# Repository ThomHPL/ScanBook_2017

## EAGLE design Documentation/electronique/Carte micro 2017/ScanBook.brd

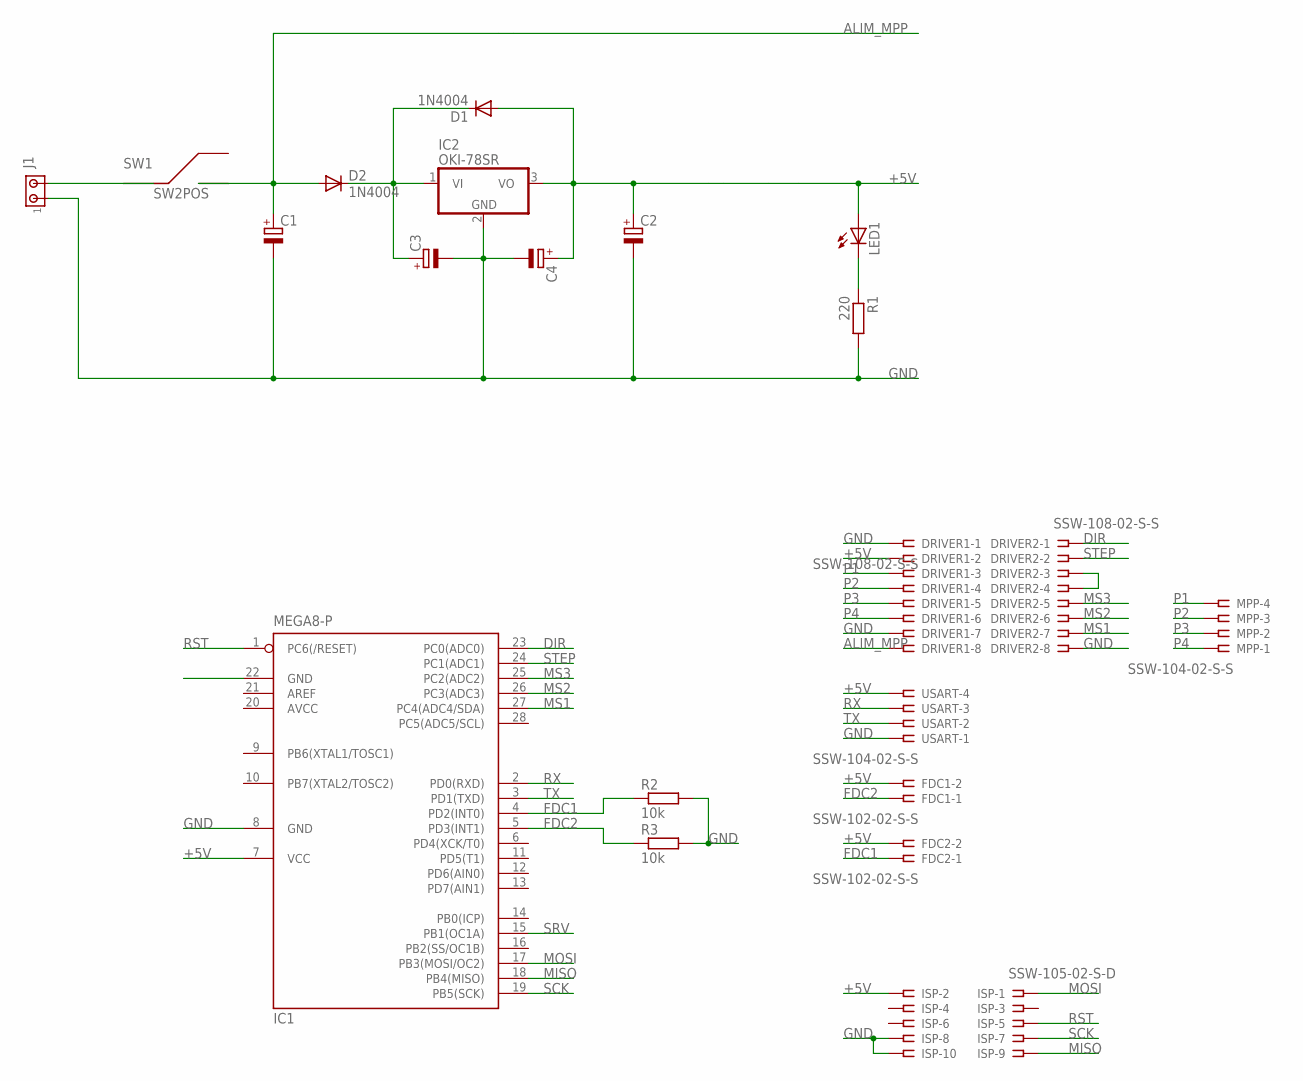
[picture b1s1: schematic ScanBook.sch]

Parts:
C1, C2: CPOL-EUE22-9AXIAL; E22-9
C3, C4: CPOL-EUTT2D4; TT2D4
D1, D2: 1N4004; DO41-10
DRIVER1, DRIVER2: SSW-108-02-S-S
FDC1, FDC2: SSW-102-02-S-S
IC1: MEGA8-P; DIL28-3
IC2: OKI-78SR; TO220V
ISP: SSW-105-02-S-D
J1: MTA02-156; 1X2MTA
LED1: LED3MM
MPP: SSW-104-02-S-S
R1: 220; 0207/10
R2, R3: 10k; 0207/10
SW1: SW2POS
USART: SSW-104-02-S-S

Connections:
+5V: C2.+, C4.+, D1.A, DRIVER1.2, FDC1.2, FDC2.2, IC1.7 (VCC), IC2.3 (VO), ISP.2, LED1.A, USART.4
ALIM_MPP: C1.+, D2.A, DRIVER1.8, SW1.3
AVCC: IC1.20 (AVCC)
DIR: DRIVER2.1, IC1.23 (PC0(ADC0))
FDC1: FDC2.1, IC1.4 (PD2(INT0)), R2.1
FDC2: FDC1.1, IC1.5 (PD3(INT1)), R3.1
GND: C1.-, C2.-, C3.-, C4.-, DRIVER1.1, DRIVER1.7, DRIVER2.8, IC1.8 (GND), IC2.2 (GND), ISP.8, ISP.10, J1.1, R1.2, R2.2, R3.2, USART.1
MISO: IC1.18 (PB4(MISO)), ISP.9
MOSI: IC1.17 (PB3(MOSI/OC2)), ISP.1
MS1: DRIVER2.7, IC1.27 (PC4(ADC4/SDA))
MS2: DRIVER2.6, IC1.26 (PC3(ADC3))
MS3: DRIVER2.5, IC1.25 (PC2(ADC2))
unnamed: J1.2, SW1.2
unnamed: C3.+, D1.C, D2.C, IC2.1 (VI)
unnamed: LED1.K (C), R1.1
unnamed: DRIVER2.3, DRIVER2.4
P1: DRIVER1.3, MPP.4
P2: DRIVER1.4, MPP.3
P3: DRIVER1.5, MPP.2
P4: DRIVER1.6, MPP.1
RST: IC1.1 (PC6(/RESET)), ISP.5
RX: IC1.2 (PD0(RXD)), USART.3
SCK: IC1.19 (PB5(SCK)), ISP.7
SRV: IC1.15 (PB1(OC1A))
STEP: DRIVER2.2, IC1.24 (PC1(ADC1))
TX: IC1.3 (PD1(TXD)), USART.2

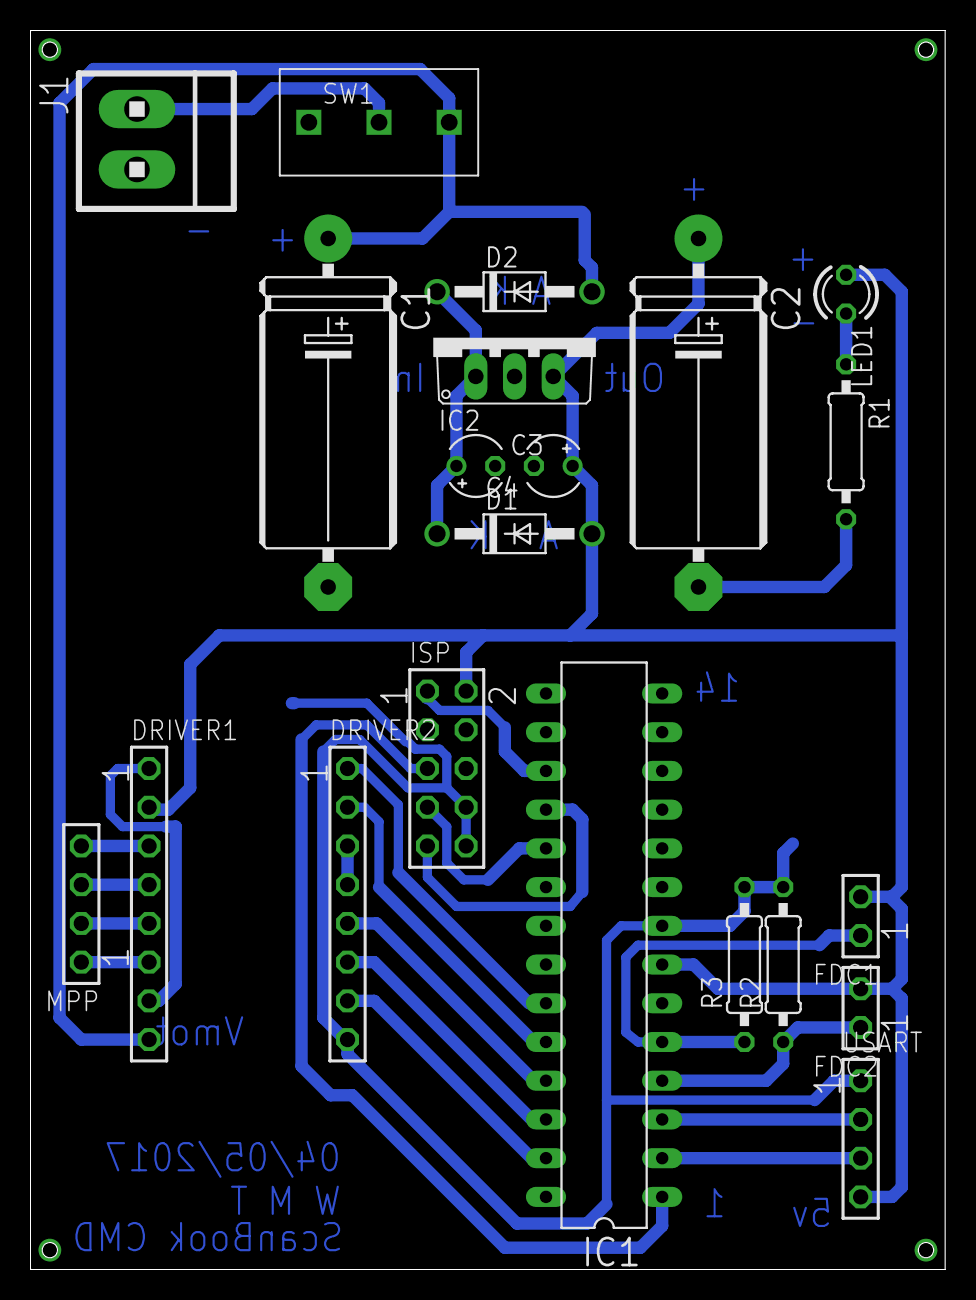
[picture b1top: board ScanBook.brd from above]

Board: 2 copper layers, 60.0 x 81.3 mm, 21 parts (0 on the bottom side), 24 nets.

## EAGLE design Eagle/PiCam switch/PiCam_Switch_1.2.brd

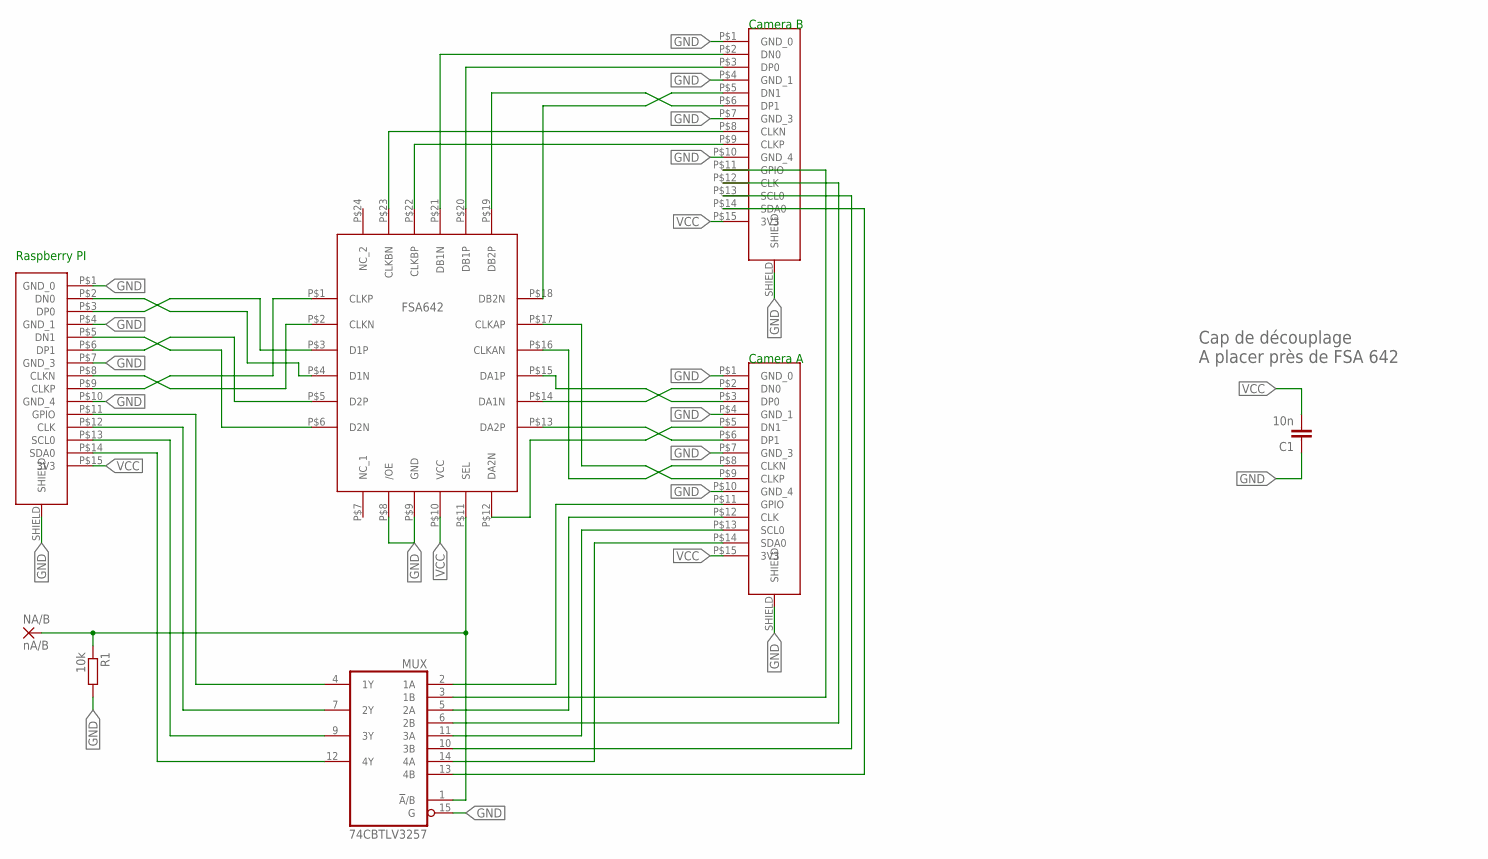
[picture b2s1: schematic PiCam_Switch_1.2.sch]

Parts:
C1: 10n; C1206
CAM_A: PICAM; FPC-CONN-15-SMD
CAM_B: PICAM; FPC-CONN-15-SMD
MUX: 74CBTLV3257; SO16
NA/B: nA/B; SMD1,27-2,54
R1: 10k; R1206
RPI: PICAM; FPC-CONN-15-SMD
U$1: FSA642; UMLP-24

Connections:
CLKA_N: CAM_A.P$8 (CLKN), U$1.P$16 (CLKAN)
CLKA_P: CAM_A.P$9 (CLKP), U$1.P$17 (CLKAP)
CLKB_N: CAM_B.P$8 (CLKN), U$1.P$23 (CLKBN)
CLKB_P: CAM_B.P$9 (CLKP), U$1.P$22 (CLKBP)
CLK_N: RPI.P$8 (CLKN), U$1.P$2 (CLKN)
CLK_P: RPI.P$9 (CLKP), U$1.P$1 (CLKP)
D0_N: RPI.P$2 (DN0), U$1.P$4 (D1N)
D0_P: RPI.P$3 (DP0), U$1.P$3 (D1P)
D1_N: RPI.P$5 (DN1), U$1.P$6 (D2N)
D1_P: RPI.P$6 (DP1), U$1.P$5 (D2P)
DA0_N: CAM_A.P$2 (DN0), U$1.P$14 (DA1N)
DA0_P: CAM_A.P$3 (DP0), U$1.P$15 (DA1P)
DA1_N: CAM_A.P$5 (DN1), U$1.P$12 (DA2N)
DA1_P: CAM_A.P$6 (DP1), U$1.P$13 (DA2P)
DB0_N: CAM_B.P$2 (DN0), U$1.P$21 (DB1N)
DB0_P: CAM_B.P$3 (DP0), U$1.P$20 (DB1P)
DB1_N: CAM_B.P$5 (DN1), U$1.P$18 (DB2N)
DB1_P: CAM_B.P$6 (DP1), U$1.P$19 (DB2P)
GND: C1.1, CAM_A.P$1 (GND_0), CAM_A.P$4 (GND_1), CAM_A.P$7 (GND_3), CAM_A.P$10 (GND_4), CAM_A.SHIELD, CAM_B.P$1 (GND_0), CAM_B.P$4 (GND_1), CAM_B.P$7 (GND_3), CAM_B.P$10 (GND_4), CAM_B.SHIELD, MUX.8 (GND), MUX.15 (G), R1.2, RPI.P$1 (GND_0), RPI.P$4 (GND_1), RPI.P$7 (GND_3), RPI.P$10 (GND_4), RPI.SHIELD, U$1.P$8 (/OE), U$1.P$9 (GND)
unnamed: MUX.1 (!A!/B), NA/B.1, R1.1, U$1.P$11 (SEL)
unnamed: MUX.4 (1Y), RPI.P$11 (GPIO)
unnamed: MUX.7 (2Y), RPI.P$12 (CLK)
unnamed: MUX.9 (3Y), RPI.P$13 (SCL0)
unnamed: MUX.12 (4Y), RPI.P$14 (SDA0)
unnamed: CAM_A.P$11 (GPIO), MUX.2 (1A)
unnamed: CAM_A.P$12 (CLK), MUX.5 (2A)
unnamed: CAM_A.P$13 (SCL0), MUX.11 (3A)
unnamed: CAM_A.P$14 (SDA0), MUX.14 (4A)
unnamed: CAM_B.P$11 (GPIO), MUX.3 (1B)
unnamed: CAM_B.P$12 (CLK), MUX.6 (2B)
unnamed: CAM_B.P$13 (SCL0), MUX.10 (3B)
unnamed: CAM_B.P$14 (SDA0), MUX.13 (4B)
VCC: C1.2, CAM_A.P$15 (3V3), CAM_B.P$15 (3V3), MUX.16 (VCC), RPI.P$15 (3V3), U$1.P$10 (VCC)

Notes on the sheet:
Raspberry PI
Camera A
Camera B
FSA642
Cap de découplage A placer près de FSA 642

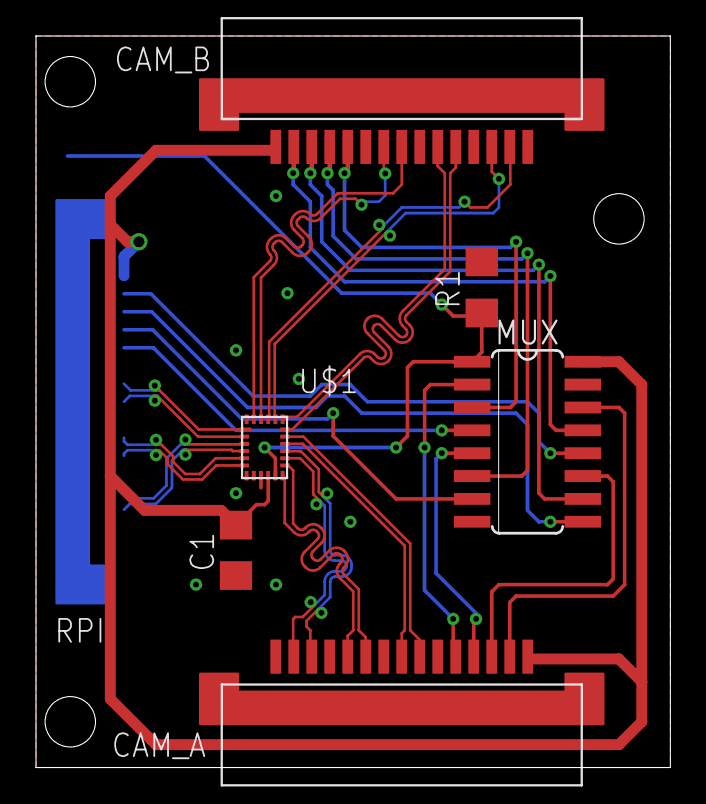
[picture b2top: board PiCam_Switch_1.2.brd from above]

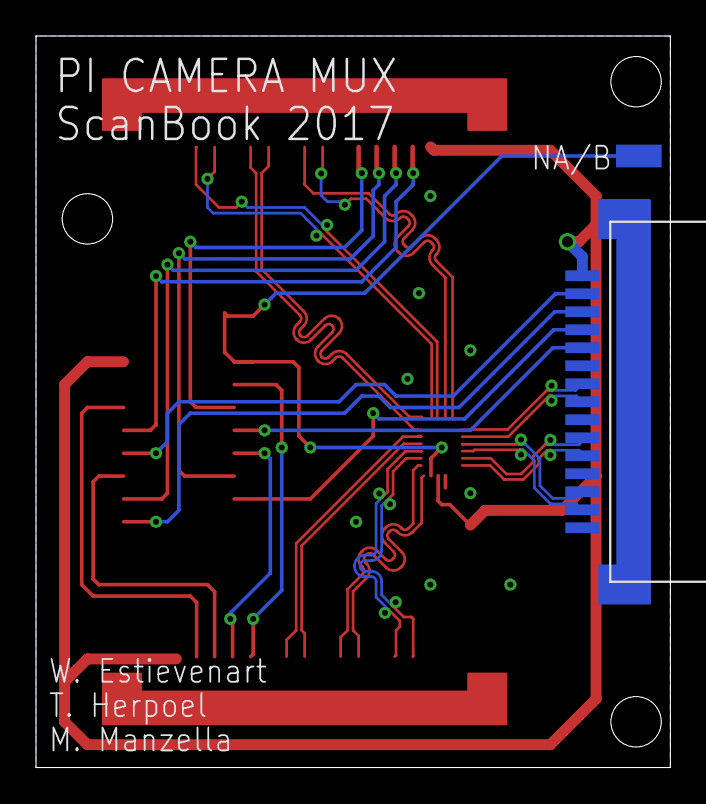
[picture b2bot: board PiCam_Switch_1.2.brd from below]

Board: 2 copper layers, 35.2 x 40.6 mm, 8 parts (2 on the bottom side), 33 nets.

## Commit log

2017-02-06 WP definition
2017-02-06 maj WP
2017-02-07 ajout planning
2017-02-07 consignes rapports
2017-02-07 bilan
2017-02-07 MAJ dual cam
2017-02-07 ajout rapport WP
2017-02-07 ajout liste estimation des prix
2017-02-07 ajout list de references bilbio
2017-02-17 test
2017-02-17 coucou
2017-02-17 remove coucou
2017-02-17 ajout du test camera 1.4
2017-03-03 ajout rapport d'avancement 3 mars
2017-03-03 ajout rendu
2017-03-06 ajout photo etat structure
2017-03-06 ajout red flags
2017-03-06 ajout rapport avancement
2017-03-06 modif rapport
2017-03-06 no message
2017-03-08 ajout corner.stl
2017-03-28 RA + docu
2017-03-28 install guide
2017-03-28 nouvelles pieces
2017-04-10 cam switch
2017-05-15 late commit...
2017-05-23 last version
